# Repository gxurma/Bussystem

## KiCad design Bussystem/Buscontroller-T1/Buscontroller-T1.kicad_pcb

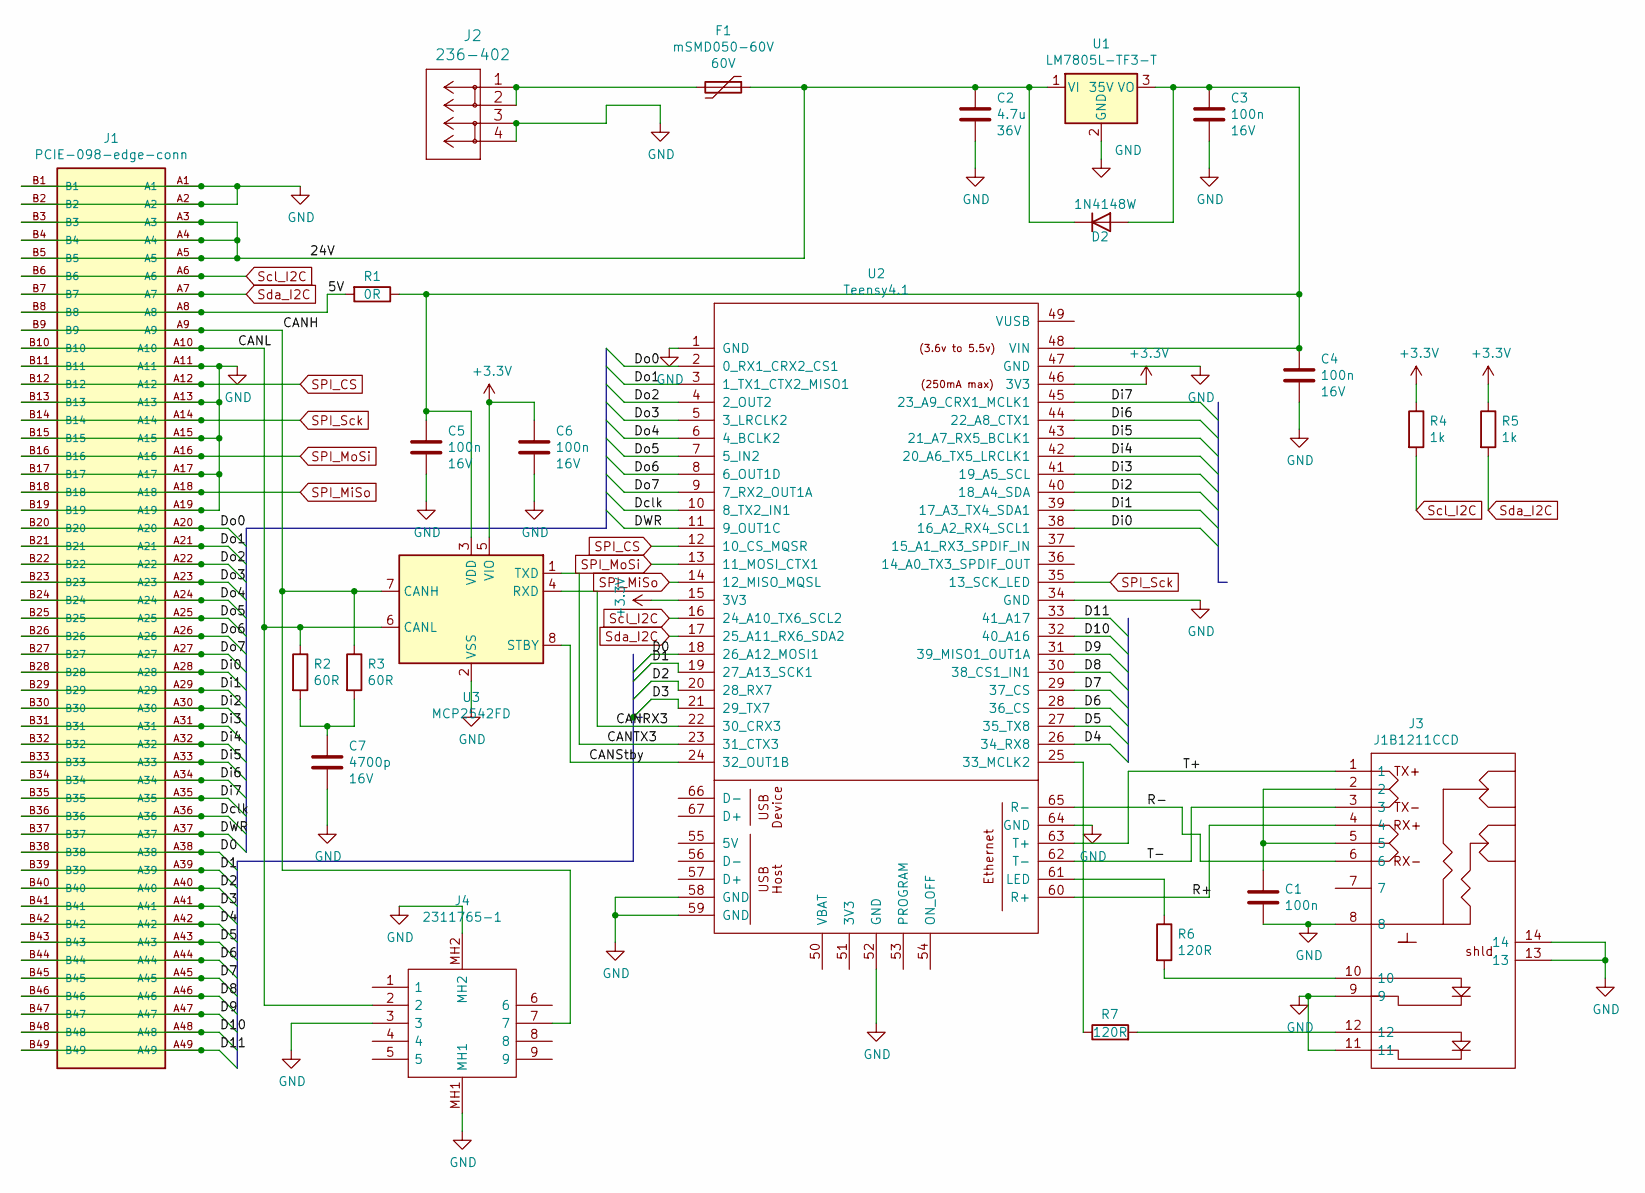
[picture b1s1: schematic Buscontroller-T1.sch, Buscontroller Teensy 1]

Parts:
C1: 100n; C_0603_HandSoldering
C2: 4.7u; C_0805_HandSoldering
C3, C4, C5, C6: 100n; C_0805_HandSoldering
C7: 4700p; C_0805_HandSoldering
D2: 1N4148W; D_SOD-123; Partnumber C81598
F1: mSMD050-60V; R_1812_HandSoldering; Partnumber C70113
J1: PCIE-098-edge-conn; pci-x_edge-x8; PARTREV D
J2: 236-402
J3: J1B1211CCD; Mouser Part Number 950-J1B1211CCD
J4: 2311765-1; 23117651; Mouser Part Number 571-2311765-1
R1: 0R; R_0805_HandSoldering
R2, R3: 60R; R_0603_HandSoldering
R4, R5: 1k; R_0603_HandSoldering
R6, R7: 120R; R_0603_HandSoldering
U1: LM7805L-TF3-T; TO-220-3_Vertical; Partnumber C71107
U2: Teensy4.1; Teensy41
U3: MCP2542FD; SOIC-8-1EP_3.9x4.9mm_Pitch1.27mm

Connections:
+3V3: C6.1, R4.1, R5.1, U2.15 (3V3), U2.46 (3V3), U3.5 (VIO)
/5V: J1.A8, J1.B8, R1.2
/24V: C2.1, D2.1 (K), F1.1, J1.A3, J1.A4, J1.A5, J1.B3, J1.B4, J1.B5, U1.1 (VI)
/CANH: J1.A9, J1.B9, J4.7, R3.1, U3.7 (CANH)
/CANL: J1.A10, J1.B10, J4.2, R2.1, U3.6 (CANL)
/CANRX3: U2.22 (30_CRX3), U3.4 (RXD)
/CANStby: U2.24 (32_OUT1B), U3.8 (STBY)
/CANTX3: U2.23 (31_CTX3), U3.1 (TXD)
/D0: J1.A38, J1.B38, U2.18 (26_A12_MOSI1)
/D1: J1.A39, J1.B39, U2.19 (27_A13_SCK1)
/D2: J1.A40, J1.B40, U2.20 (28_RX7)
/D3: J1.A41, J1.B41, U2.21 (29_TX7)
/D4: J1.A42, J1.B42, U2.26 (34_RX8)
/D5: J1.A43, J1.B43, U2.27 (35_TX8)
/D6: J1.A44, J1.B44, U2.28 (36_CS)
/D7: J1.A45, J1.B45, U2.29 (37_CS)
/D8: J1.A46, J1.B46, U2.30 (38_CS1_IN1)
/D9: J1.A47, J1.B47, U2.31 (39_MISO1_OUT1A)
/D10: J1.A48, J1.B48, U2.32 (40_A16)
/D11: J1.A49, J1.B49, U2.33 (41_A17)
/DWR: J1.A37, J1.B37, U2.11 (9_OUT1C)
/Dclk: J1.A36, J1.B36, U2.10 (8_TX2_IN1)
/Di0: J1.A28, J1.B28, U2.38 (16_A2_RX4_SCL1)
/Di1: J1.A29, J1.B29, U2.39 (17_A3_TX4_SDA1)
/Di2: J1.A30, J1.B30, U2.40 (18_A4_SDA)
/Di3: J1.A31, J1.B31, U2.41 (19_A5_SCL)
/Di4: J1.A32, J1.B32, U2.42 (20_A6_TX5_LRCLK1)
/Di5: J1.A33, J1.B33, U2.43 (21_A7_RX5_BCLK1)
/Di6: J1.A34, J1.B34, U2.44 (22_A8_CTX1)
/Di7: J1.A35, J1.B35, U2.45 (23_A9_CRX1_MCLK1)
/Do0: J1.A20, J1.B20, U2.2 (0_RX1_CRX2_CS1)
/Do1: J1.A21, J1.B21, U2.3 (1_TX1_CTX2_MISO1)
/Do2: J1.A22, J1.B22, U2.4 (2_OUT2)
/Do3: J1.A23, J1.B23, U2.5 (3_LRCLK2)
/Do4: J1.A24, J1.B24, U2.6 (4_BCLK2)
/Do5: J1.A25, J1.B25, U2.7 (5_IN2)
/Do6: J1.A26, J1.B26, U2.8 (6_OUT1D)
/Do7: J1.A27, J1.B27, U2.9 (7_RX2_OUT1A)
/R+: J3.4, U2.60 (R+)
/R-: J3.6, U2.65 (R-)
/T+: J3.1, U2.63 (T+)
/T-: J3.3, U2.62 (T-)
GND: C1.2, C2.2, C3.2, C4.2, C5.2, C6.2, C7.2, J1.A1, J1.A2, J1.A11, J1.A13, J1.A15, J1.A17, J1.A19, J1.B1, J1.B2, J1.B11, J1.B13, J1.B15, J1.B17, J1.B19, J2.3, J2.4, J3.8, J3.9, J3.11, J3.13, J3.14, J4.3, J4.MH1, J4.MH2, U1.2 (GND), U2.1 (GND), U2.34 (GND), U2.47 (GND), U2.52 (GND), U2.58 (GND), U2.59 (GND), U2.64 (GND), U3.2 (VSS), U3.9 (VSS)
unnamed: C1.1, J3.2, J3.5
unnamed: C3.1, C4.1, C5.1, D2.2 (A), R1.1, U1.3 (VO), U2.48 (VIN), U3.3 (VDD)
unnamed: C7.1, R2.2, R3.2
unnamed: F1.2, J2.1, J2.2
unnamed: J3.10, R6.2
unnamed: J3.12, R7.2
unnamed: R6.1, U2.61 (LED)
unnamed: R7.1, U2.25 (33_MCLK2)
SPI_CS: J1.A12, J1.B12, U2.12 (10_CS_MQSR)
SPI_MiSo: J1.A18, J1.B18, U2.14 (12_MISO_MQSL)
SPI_MoSi: J1.A16, J1.B16, U2.13 (11_MOSI_CTX1)
SPI_Sck: J1.A14, J1.B14, U2.35 (13_SCK_LED)
Scl_I2C: J1.A6, J1.B6, R4.2, U2.16 (24_A10_TX6_SCL2)
Sda_I2C: J1.A7, J1.B7, R5.2, U2.17 (25_A11_RX6_SDA2)

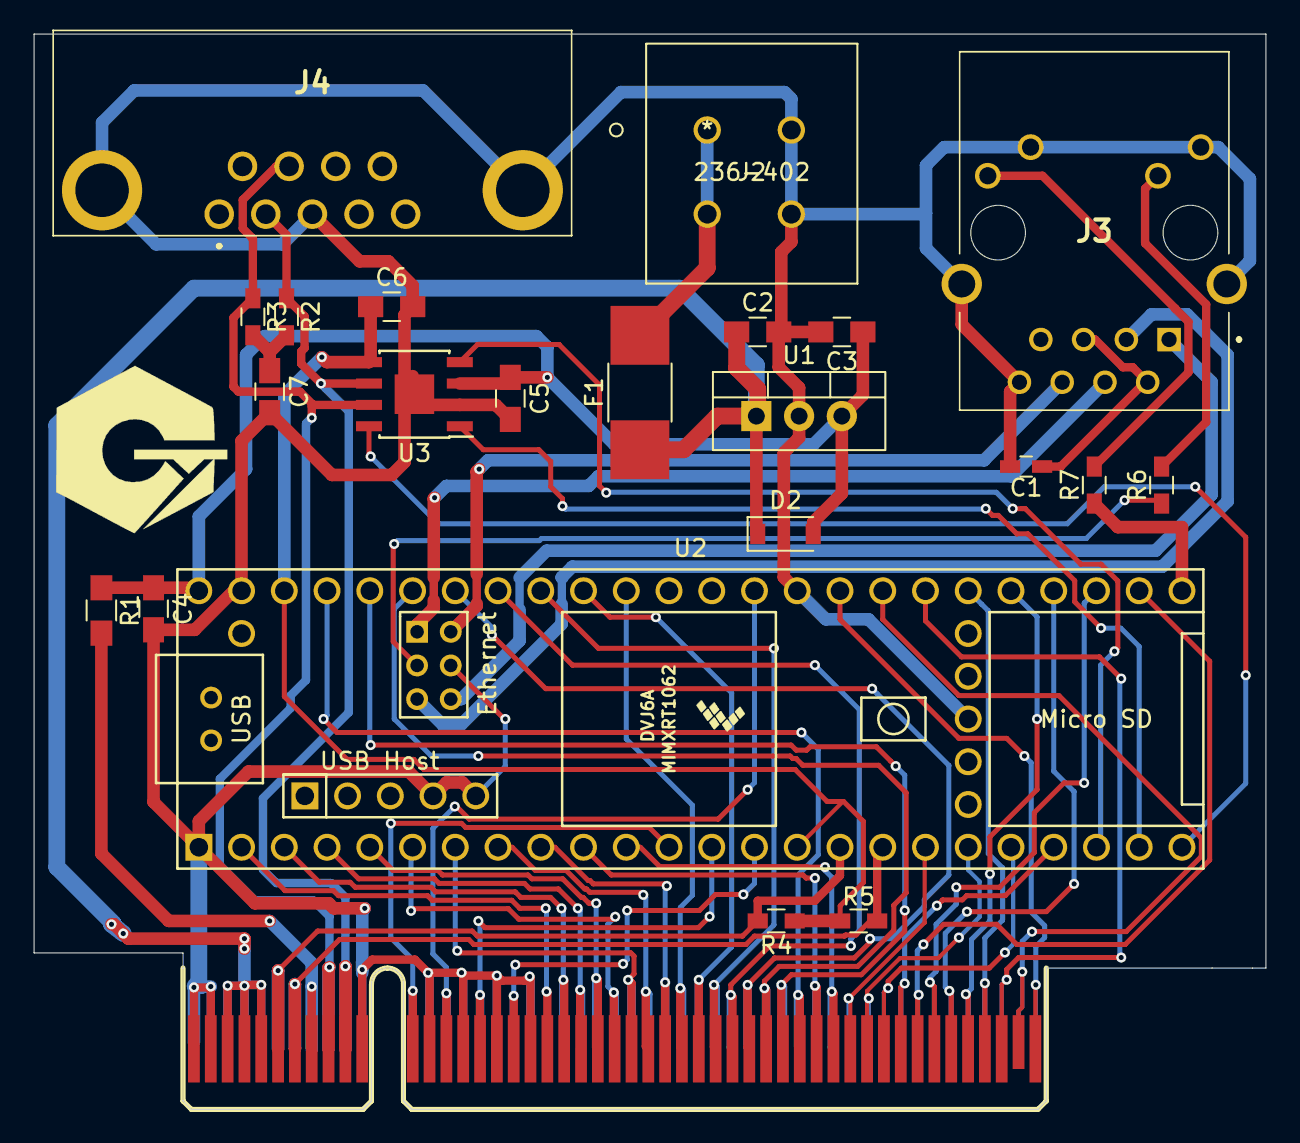
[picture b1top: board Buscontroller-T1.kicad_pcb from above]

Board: 2 copper layers, 73.2 x 63.9 mm, 23 parts (0 on the bottom side), 57 nets.

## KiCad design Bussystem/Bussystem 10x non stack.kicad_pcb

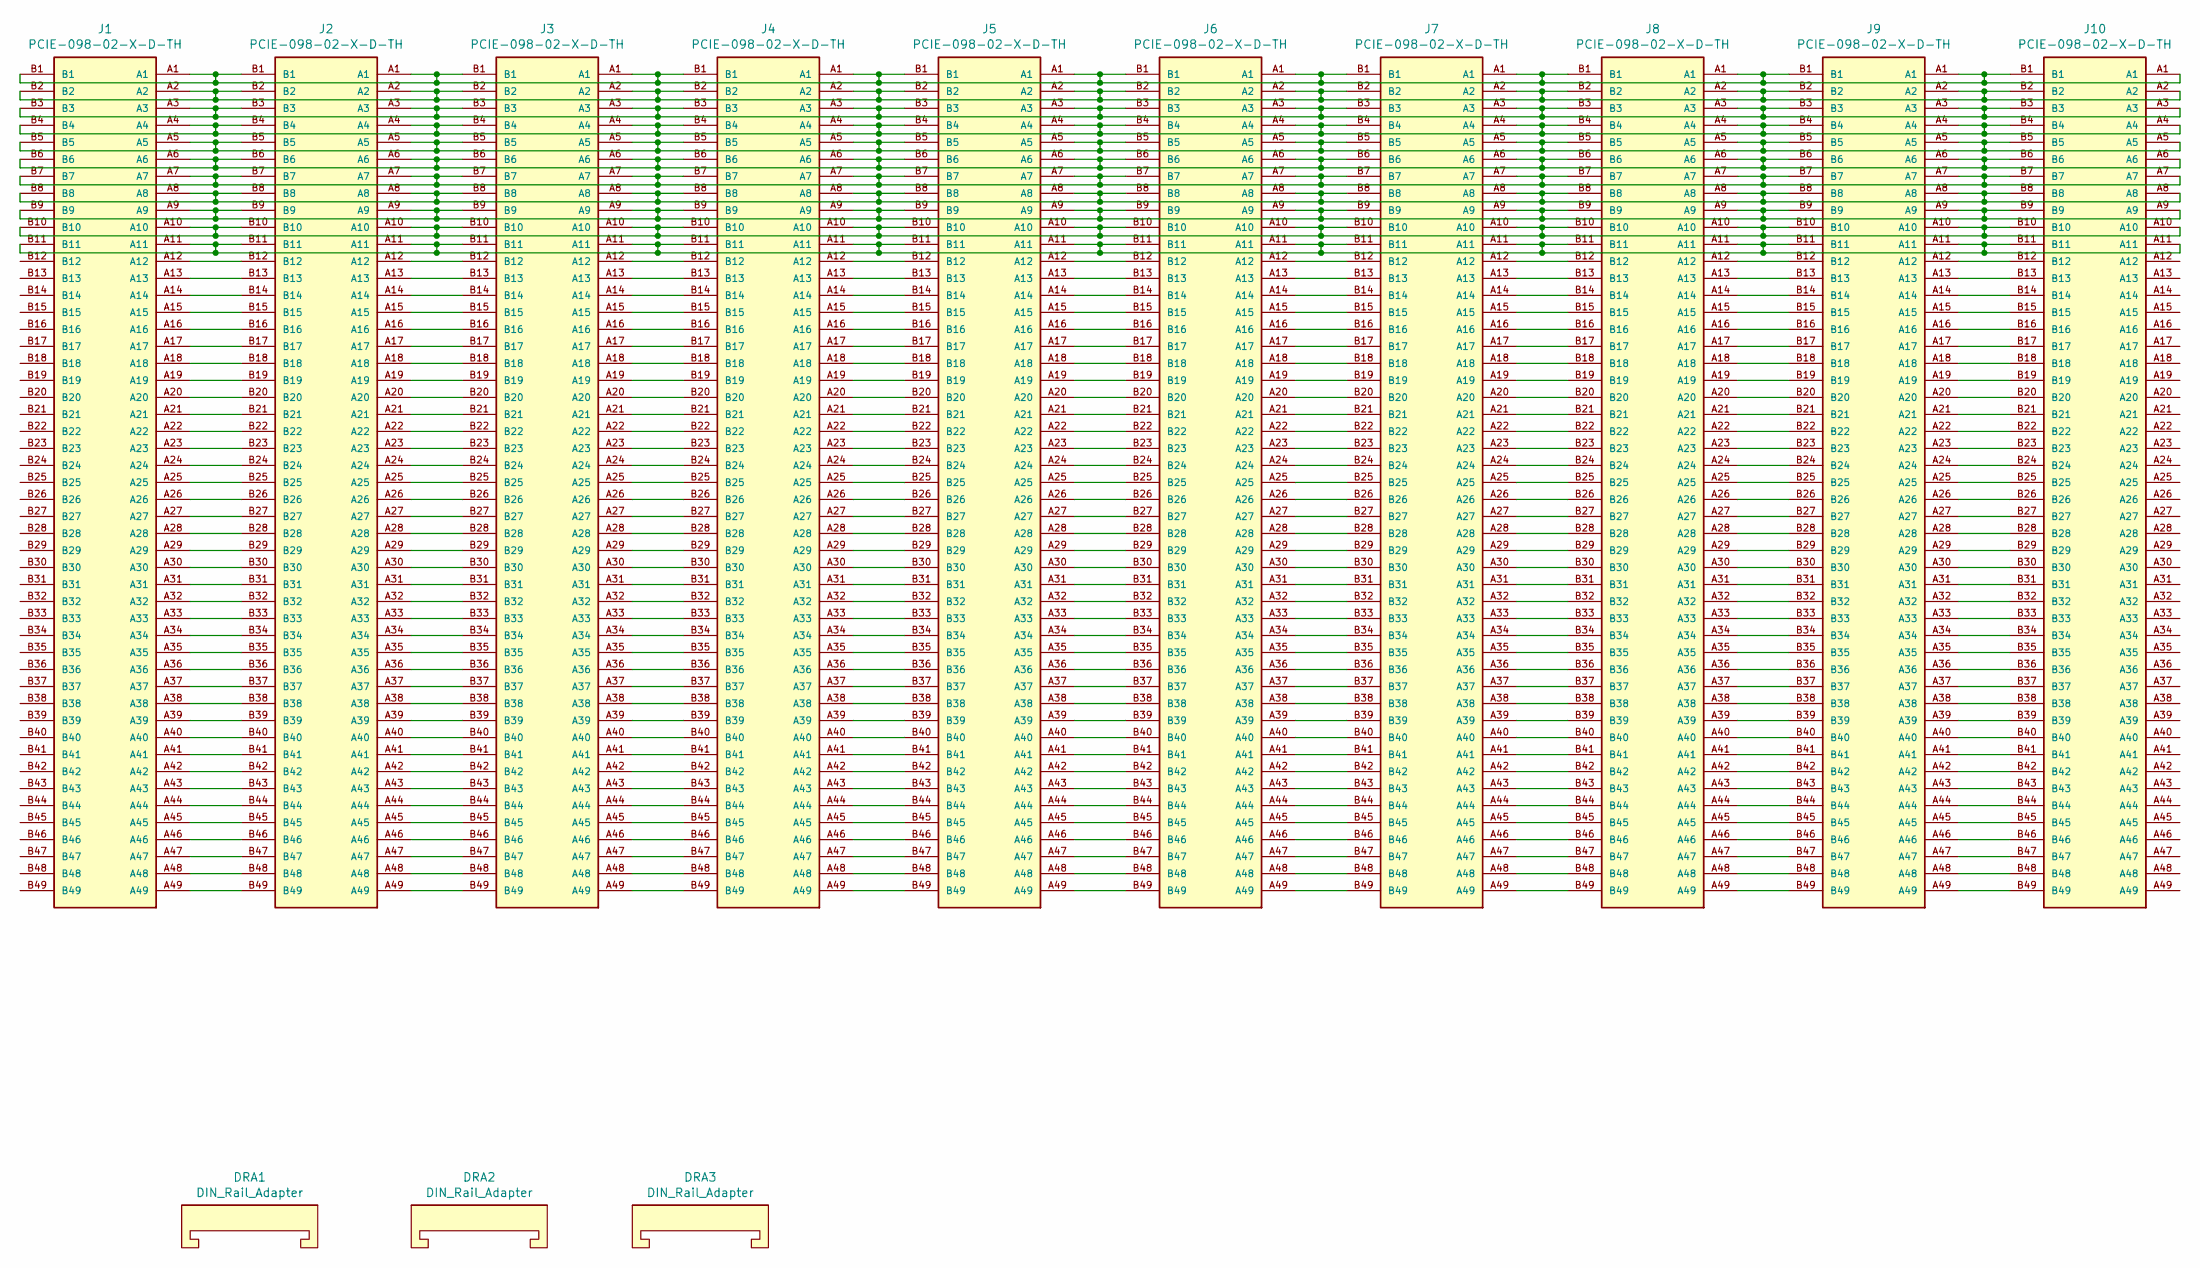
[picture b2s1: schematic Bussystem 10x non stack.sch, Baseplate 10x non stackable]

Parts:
DRA1, DRA2, DRA3: DIN_Rail_Adapter; DIN_Mount
J1, J2, J3, J4, J5, J6, J7, J8, J9, J10: PCIE-098-02-X-D-TH; SAMTEC_PCIE-098-02-X-D-TH; PARTREV D

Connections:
unnamed: J1.A1, J1.B1, J2.A1, J2.B1, J3.A1, J3.B1, J4.A1, J4.B1, J5.A1, J5.B1, J6.A1, J6.B1, J7.A1, J7.B1, J8.A1, J8.B1, J9.A1, J9.B1, J10.A1, J10.B1
unnamed: J1.A2, J1.B2, J2.A2, J2.B2, J3.A2, J3.B2, J4.A2, J4.B2, J5.A2, J5.B2, J6.A2, J6.B2, J7.A2, J7.B2, J8.A2, J8.B2, J9.A2, J9.B2, J10.A2, J10.B2
unnamed: J1.A3, J1.B3, J2.A3, J2.B3, J3.A3, J3.B3, J4.A3, J4.B3, J5.A3, J5.B3, J6.A3, J6.B3, J7.A3, J7.B3, J8.A3, J8.B3, J9.A3, J9.B3, J10.A3, J10.B3
unnamed: J1.A4, J1.B4, J2.A4, J2.B4, J3.A4, J3.B4, J4.A4, J4.B4, J5.A4, J5.B4, J6.A4, J6.B4, J7.A4, J7.B4, J8.A4, J8.B4, J9.A4, J9.B4, J10.A4, J10.B4
unnamed: J1.A5, J1.B5, J2.A5, J2.B5, J3.A5, J3.B5, J4.A5, J4.B5, J5.A5, J5.B5, J6.A5, J6.B5, J7.A5, J7.B5, J8.A5, J8.B5, J9.A5, J9.B5, J10.A5, J10.B5
unnamed: J1.A6, J1.B6, J2.A6, J2.B6, J3.A6, J3.B6, J4.A6, J4.B6, J5.A6, J5.B6, J6.A6, J6.B6, J7.A6, J7.B6, J8.A6, J8.B6, J9.A6, J9.B6, J10.A6, J10.B6
unnamed: J1.A7, J1.B7, J2.A7, J2.B7, J3.A7, J3.B7, J4.A7, J4.B7, J5.A7, J5.B7, J6.A7, J6.B7, J7.A7, J7.B7, J8.A7, J8.B7, J9.A7, J9.B7, J10.A7, J10.B7
unnamed: J1.A8, J1.B8, J2.A8, J2.B8, J3.A8, J3.B8, J4.A8, J4.B8, J5.A8, J5.B8, J6.A8, J6.B8, J7.A8, J7.B8, J8.A8, J8.B8, J9.A8, J9.B8, J10.A8, J10.B8
unnamed: J1.A9, J1.B9, J2.A9, J2.B9, J3.A9, J3.B9, J4.A9, J4.B9, J5.A9, J5.B9, J6.A9, J6.B9, J7.A9, J7.B9, J8.A9, J8.B9, J9.A9, J9.B9, J10.A9, J10.B9
unnamed: J1.A10, J1.B10, J2.A10, J2.B10, J3.A10, J3.B10, J4.A10, J4.B10, J5.A10, J5.B10, J6.A10, J6.B10, J7.A10, J7.B10, J8.A10, J8.B10, J9.A10, J9.B10, J10.A10, J10.B10
unnamed: J1.A11, J1.B11, J2.A11, J2.B11, J3.A11, J3.B11, J4.A11, J4.B11, J5.A11, J5.B11, J6.A11, J6.B11, J7.A11, J7.B11, J8.A11, J8.B11, J9.A11, J9.B11, J10.A11, J10.B11
unnamed: J1.A12, J2.B12
unnamed: J1.A13, J2.B13
unnamed: J1.A14, J2.B14
unnamed: J1.A15, J2.B15
unnamed: J1.A16, J2.B16
unnamed: J1.A17, J2.B17
unnamed: J1.A18, J2.B18
unnamed: J1.A19, J2.B19
unnamed: J1.A20, J2.B20
unnamed: J1.A21, J2.B21
unnamed: J1.A22, J2.B22
unnamed: J1.A23, J2.B23
unnamed: J1.A24, J2.B24
unnamed: J1.A25, J2.B25
unnamed: J1.A26, J2.B26
unnamed: J1.A27, J2.B27
unnamed: J1.A28, J2.B28
unnamed: J1.A29, J2.B29
unnamed: J1.A30, J2.B30
unnamed: J1.A31, J2.B31
unnamed: J1.A32, J2.B32
unnamed: J1.A33, J2.B33
unnamed: J1.A34, J2.B34
unnamed: J1.A35, J2.B35
unnamed: J1.A36, J2.B36
unnamed: J1.A37, J2.B37
unnamed: J1.A38, J2.B38
unnamed: J1.A39, J2.B39
unnamed: J1.A40, J2.B40
unnamed: J1.A41, J2.B41
unnamed: J1.A42, J2.B42
unnamed: J1.A43, J2.B43
unnamed: J1.A44, J2.B44
unnamed: J1.A45, J2.B45
unnamed: J1.A46, J2.B46
unnamed: J1.A47, J2.B47
unnamed: J1.A48, J2.B48
unnamed: J1.A49, J2.B49
unnamed: J2.A12, J3.B12
unnamed: J2.A13, J3.B13
unnamed: J2.A14, J3.B14
unnamed: J2.A15, J3.B15
unnamed: J2.A16, J3.B16
unnamed: J2.A17, J3.B17
unnamed: J2.A18, J3.B18
unnamed: J2.A19, J3.B19
unnamed: J2.A20, J3.B20
unnamed: J2.A21, J3.B21
unnamed: J2.A22, J3.B22
unnamed: J2.A23, J3.B23
unnamed: J2.A24, J3.B24
unnamed: J2.A25, J3.B25
unnamed: J2.A26, J3.B26
unnamed: J2.A27, J3.B27
unnamed: J2.A28, J3.B28
unnamed: J2.A29, J3.B29
unnamed: J2.A30, J3.B30
unnamed: J2.A31, J3.B31
unnamed: J2.A32, J3.B32
unnamed: J2.A33, J3.B33
unnamed: J2.A34, J3.B34
unnamed: J2.A35, J3.B35
unnamed: J2.A36, J3.B36
unnamed: J2.A37, J3.B37
unnamed: J2.A38, J3.B38
unnamed: J2.A39, J3.B39
unnamed: J2.A40, J3.B40
unnamed: J2.A41, J3.B41
unnamed: J2.A42, J3.B42
unnamed: J2.A43, J3.B43
unnamed: J2.A44, J3.B44
unnamed: J2.A45, J3.B45
unnamed: J2.A46, J3.B46
unnamed: J2.A47, J3.B47
unnamed: J2.A48, J3.B48
unnamed: J2.A49, J3.B49
unnamed: J3.A12, J4.B12
unnamed: J3.A13, J4.B13
unnamed: J3.A14, J4.B14
unnamed: J3.A15, J4.B15
unnamed: J3.A16, J4.B16
unnamed: J3.A17, J4.B17
unnamed: J3.A18, J4.B18
unnamed: J3.A19, J4.B19
unnamed: J3.A20, J4.B20
unnamed: J3.A21, J4.B21
unnamed: J3.A22, J4.B22
unnamed: J3.A23, J4.B23
unnamed: J3.A24, J4.B24
unnamed: J3.A25, J4.B25
unnamed: J3.A26, J4.B26
unnamed: J3.A27, J4.B27
unnamed: J3.A28, J4.B28
unnamed: J3.A29, J4.B29
unnamed: J3.A30, J4.B30
unnamed: J3.A31, J4.B31
unnamed: J3.A32, J4.B32
unnamed: J3.A33, J4.B33
unnamed: J3.A34, J4.B34
unnamed: J3.A35, J4.B35
unnamed: J3.A36, J4.B36
unnamed: J3.A37, J4.B37
unnamed: J3.A38, J4.B38
unnamed: J3.A39, J4.B39
unnamed: J3.A40, J4.B40
unnamed: J3.A41, J4.B41
unnamed: J3.A42, J4.B42
unnamed: J3.A43, J4.B43
unnamed: J3.A44, J4.B44
unnamed: J3.A45, J4.B45
unnamed: J3.A46, J4.B46
unnamed: J3.A47, J4.B47
unnamed: J3.A48, J4.B48
unnamed: J3.A49, J4.B49
unnamed: J4.A12, J5.B12
unnamed: J4.A13, J5.B13
unnamed: J4.A14, J5.B14
unnamed: J4.A15, J5.B15
unnamed: J4.A16, J5.B16
unnamed: J4.A17, J5.B17
unnamed: J4.A18, J5.B18
unnamed: J4.A19, J5.B19
unnamed: J4.A20, J5.B20
unnamed: J4.A21, J5.B21
unnamed: J4.A22, J5.B22
unnamed: J4.A23, J5.B23
unnamed: J4.A24, J5.B24
unnamed: J4.A25, J5.B25
unnamed: J4.A26, J5.B26
unnamed: J4.A27, J5.B27
unnamed: J4.A28, J5.B28
unnamed: J4.A29, J5.B29
unnamed: J4.A30, J5.B30
unnamed: J4.A31, J5.B31
unnamed: J4.A32, J5.B32
unnamed: J4.A33, J5.B33
unnamed: J4.A34, J5.B34
unnamed: J4.A35, J5.B35
unnamed: J4.A36, J5.B36
unnamed: J4.A37, J5.B37
unnamed: J4.A38, J5.B38
unnamed: J4.A39, J5.B39
unnamed: J4.A40, J5.B40
unnamed: J4.A41, J5.B41
unnamed: J4.A42, J5.B42
unnamed: J4.A43, J5.B43
unnamed: J4.A44, J5.B44
unnamed: J4.A45, J5.B45
unnamed: J4.A46, J5.B46
unnamed: J4.A47, J5.B47
unnamed: J4.A48, J5.B48
unnamed: J4.A49, J5.B49
unnamed: J5.A12, J6.B12
unnamed: J5.A13, J6.B13
unnamed: J5.A14, J6.B14
unnamed: J5.A15, J6.B15
unnamed: J5.A16, J6.B16
unnamed: J5.A17, J6.B17
unnamed: J5.A18, J6.B18
unnamed: J5.A19, J6.B19
unnamed: J5.A20, J6.B20
unnamed: J5.A21, J6.B21
unnamed: J5.A22, J6.B22
unnamed: J5.A23, J6.B23
unnamed: J5.A24, J6.B24
unnamed: J5.A25, J6.B25
unnamed: J5.A26, J6.B26
unnamed: J5.A27, J6.B27
unnamed: J5.A28, J6.B28
unnamed: J5.A29, J6.B29
unnamed: J5.A30, J6.B30
unnamed: J5.A31, J6.B31
unnamed: J5.A32, J6.B32
unnamed: J5.A33, J6.B33
unnamed: J5.A34, J6.B34
unnamed: J5.A35, J6.B35
unnamed: J5.A36, J6.B36
unnamed: J5.A37, J6.B37
unnamed: J5.A38, J6.B38
unnamed: J5.A39, J6.B39
unnamed: J5.A40, J6.B40
unnamed: J5.A41, J6.B41
unnamed: J5.A42, J6.B42
unnamed: J5.A43, J6.B43
unnamed: J5.A44, J6.B44
unnamed: J5.A45, J6.B45
unnamed: J5.A46, J6.B46
unnamed: J5.A47, J6.B47
unnamed: J5.A48, J6.B48
unnamed: J5.A49, J6.B49
unnamed: J6.A12, J7.B12
unnamed: J6.A13, J7.B13
unnamed: J6.A14, J7.B14
unnamed: J6.A15, J7.B15
unnamed: J6.A16, J7.B16
unnamed: J6.A17, J7.B17
unnamed: J6.A18, J7.B18
unnamed: J6.A19, J7.B19
unnamed: J6.A20, J7.B20
unnamed: J6.A21, J7.B21
unnamed: J6.A22, J7.B22
unnamed: J6.A23, J7.B23
unnamed: J6.A24, J7.B24
unnamed: J6.A25, J7.B25
unnamed: J6.A26, J7.B26
unnamed: J6.A27, J7.B27
unnamed: J6.A28, J7.B28
unnamed: J6.A29, J7.B29
unnamed: J6.A30, J7.B30
unnamed: J6.A31, J7.B31
unnamed: J6.A32, J7.B32
unnamed: J6.A33, J7.B33
unnamed: J6.A34, J7.B34
unnamed: J6.A35, J7.B35
unnamed: J6.A36, J7.B36
unnamed: J6.A37, J7.B37
unnamed: J6.A38, J7.B38
unnamed: J6.A39, J7.B39
unnamed: J6.A40, J7.B40
unnamed: J6.A41, J7.B41
unnamed: J6.A42, J7.B42
unnamed: J6.A43, J7.B43
unnamed: J6.A44, J7.B44
unnamed: J6.A45, J7.B45
unnamed: J6.A46, J7.B46
unnamed: J6.A47, J7.B47
unnamed: J6.A48, J7.B48
unnamed: J6.A49, J7.B49
unnamed: J7.A12, J8.B12
unnamed: J7.A13, J8.B13
unnamed: J7.A14, J8.B14
unnamed: J7.A15, J8.B15
unnamed: J7.A16, J8.B16
unnamed: J7.A17, J8.B17
unnamed: J7.A18, J8.B18
unnamed: J7.A19, J8.B19
unnamed: J7.A20, J8.B20
unnamed: J7.A21, J8.B21
unnamed: J7.A22, J8.B22
unnamed: J7.A23, J8.B23
unnamed: J7.A24, J8.B24
unnamed: J7.A25, J8.B25
unnamed: J7.A26, J8.B26
unnamed: J7.A27, J8.B27
unnamed: J7.A28, J8.B28
unnamed: J7.A29, J8.B29
unnamed: J7.A30, J8.B30
unnamed: J7.A31, J8.B31
unnamed: J7.A32, J8.B32
unnamed: J7.A33, J8.B33
unnamed: J7.A34, J8.B34
unnamed: J7.A35, J8.B35
unnamed: J7.A36, J8.B36
unnamed: J7.A37, J8.B37
unnamed: J7.A38, J8.B38
unnamed: J7.A39, J8.B39
unnamed: J7.A40, J8.B40
unnamed: J7.A41, J8.B41
unnamed: J7.A42, J8.B42
unnamed: J7.A43, J8.B43
unnamed: J7.A44, J8.B44
unnamed: J7.A45, J8.B45
unnamed: J7.A46, J8.B46
unnamed: J7.A47, J8.B47
unnamed: J7.A48, J8.B48
unnamed: J7.A49, J8.B49
unnamed: J8.A12, J9.B12
unnamed: J8.A13, J9.B13
unnamed: J8.A14, J9.B14
unnamed: J8.A15, J9.B15
unnamed: J8.A16, J9.B16
unnamed: J8.A17, J9.B17
unnamed: J8.A18, J9.B18
unnamed: J8.A19, J9.B19
unnamed: J8.A20, J9.B20
unnamed: J8.A21, J9.B21
unnamed: J8.A22, J9.B22
unnamed: J8.A23, J9.B23
unnamed: J8.A24, J9.B24
unnamed: J8.A25, J9.B25
unnamed: J8.A26, J9.B26
unnamed: J8.A27, J9.B27
unnamed: J8.A28, J9.B28
unnamed: J8.A29, J9.B29
unnamed: J8.A30, J9.B30
unnamed: J8.A31, J9.B31
unnamed: J8.A32, J9.B32
unnamed: J8.A33, J9.B33
unnamed: J8.A34, J9.B34
unnamed: J8.A35, J9.B35
unnamed: J8.A36, J9.B36
unnamed: J8.A37, J9.B37
unnamed: J8.A38, J9.B38
unnamed: J8.A39, J9.B39
unnamed: J8.A40, J9.B40
unnamed: J8.A41, J9.B41
unnamed: J8.A42, J9.B42
unnamed: J8.A43, J9.B43
unnamed: J8.A44, J9.B44
unnamed: J8.A45, J9.B45
unnamed: J8.A46, J9.B46
unnamed: J8.A47, J9.B47
unnamed: J8.A48, J9.B48
unnamed: J8.A49, J9.B49
unnamed: J9.A12, J10.B12
unnamed: J9.A13, J10.B13
unnamed: J9.A14, J10.B14
unnamed: J9.A15, J10.B15
unnamed: J9.A16, J10.B16
unnamed: J9.A17, J10.B17
unnamed: J9.A18, J10.B18
unnamed: J9.A19, J10.B19
unnamed: J9.A20, J10.B20
unnamed: J9.A21, J10.B21
unnamed: J9.A22, J10.B22
unnamed: J9.A23, J10.B23
unnamed: J9.A24, J10.B24
unnamed: J9.A25, J10.B25
unnamed: J9.A26, J10.B26
unnamed: J9.A27, J10.B27
unnamed: J9.A28, J10.B28
unnamed: J9.A29, J10.B29
unnamed: J9.A30, J10.B30
unnamed: J9.A31, J10.B31
unnamed: J9.A32, J10.B32
unnamed: J9.A33, J10.B33
unnamed: J9.A34, J10.B34
unnamed: J9.A35, J10.B35
unnamed: J9.A36, J10.B36
unnamed: J9.A37, J10.B37
unnamed: J9.A38, J10.B38
unnamed: J9.A39, J10.B39
unnamed: J9.A40, J10.B40
unnamed: J9.A41, J10.B41
unnamed: J9.A42, J10.B42
unnamed: J9.A43, J10.B43
unnamed: J9.A44, J10.B44
unnamed: J9.A45, J10.B45
unnamed: J9.A46, J10.B46
unnamed: J9.A47, J10.B47
unnamed: J9.A48, J10.B48
unnamed: J9.A49, J10.B49

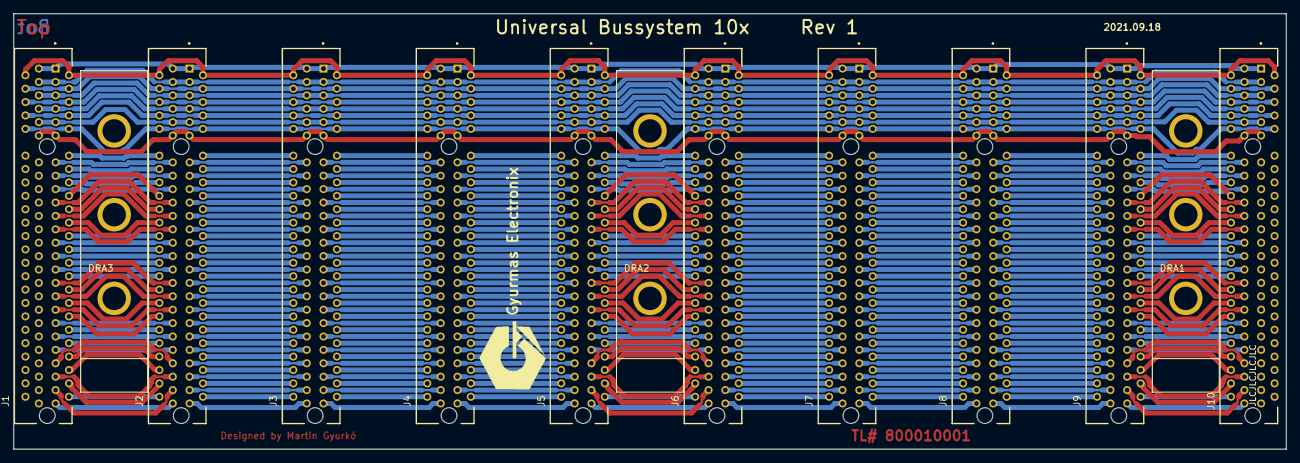
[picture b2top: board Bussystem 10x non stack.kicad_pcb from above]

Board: 2 copper layers, 190.0 x 65.0 mm, 13 parts (0 on the bottom side), 353 nets.

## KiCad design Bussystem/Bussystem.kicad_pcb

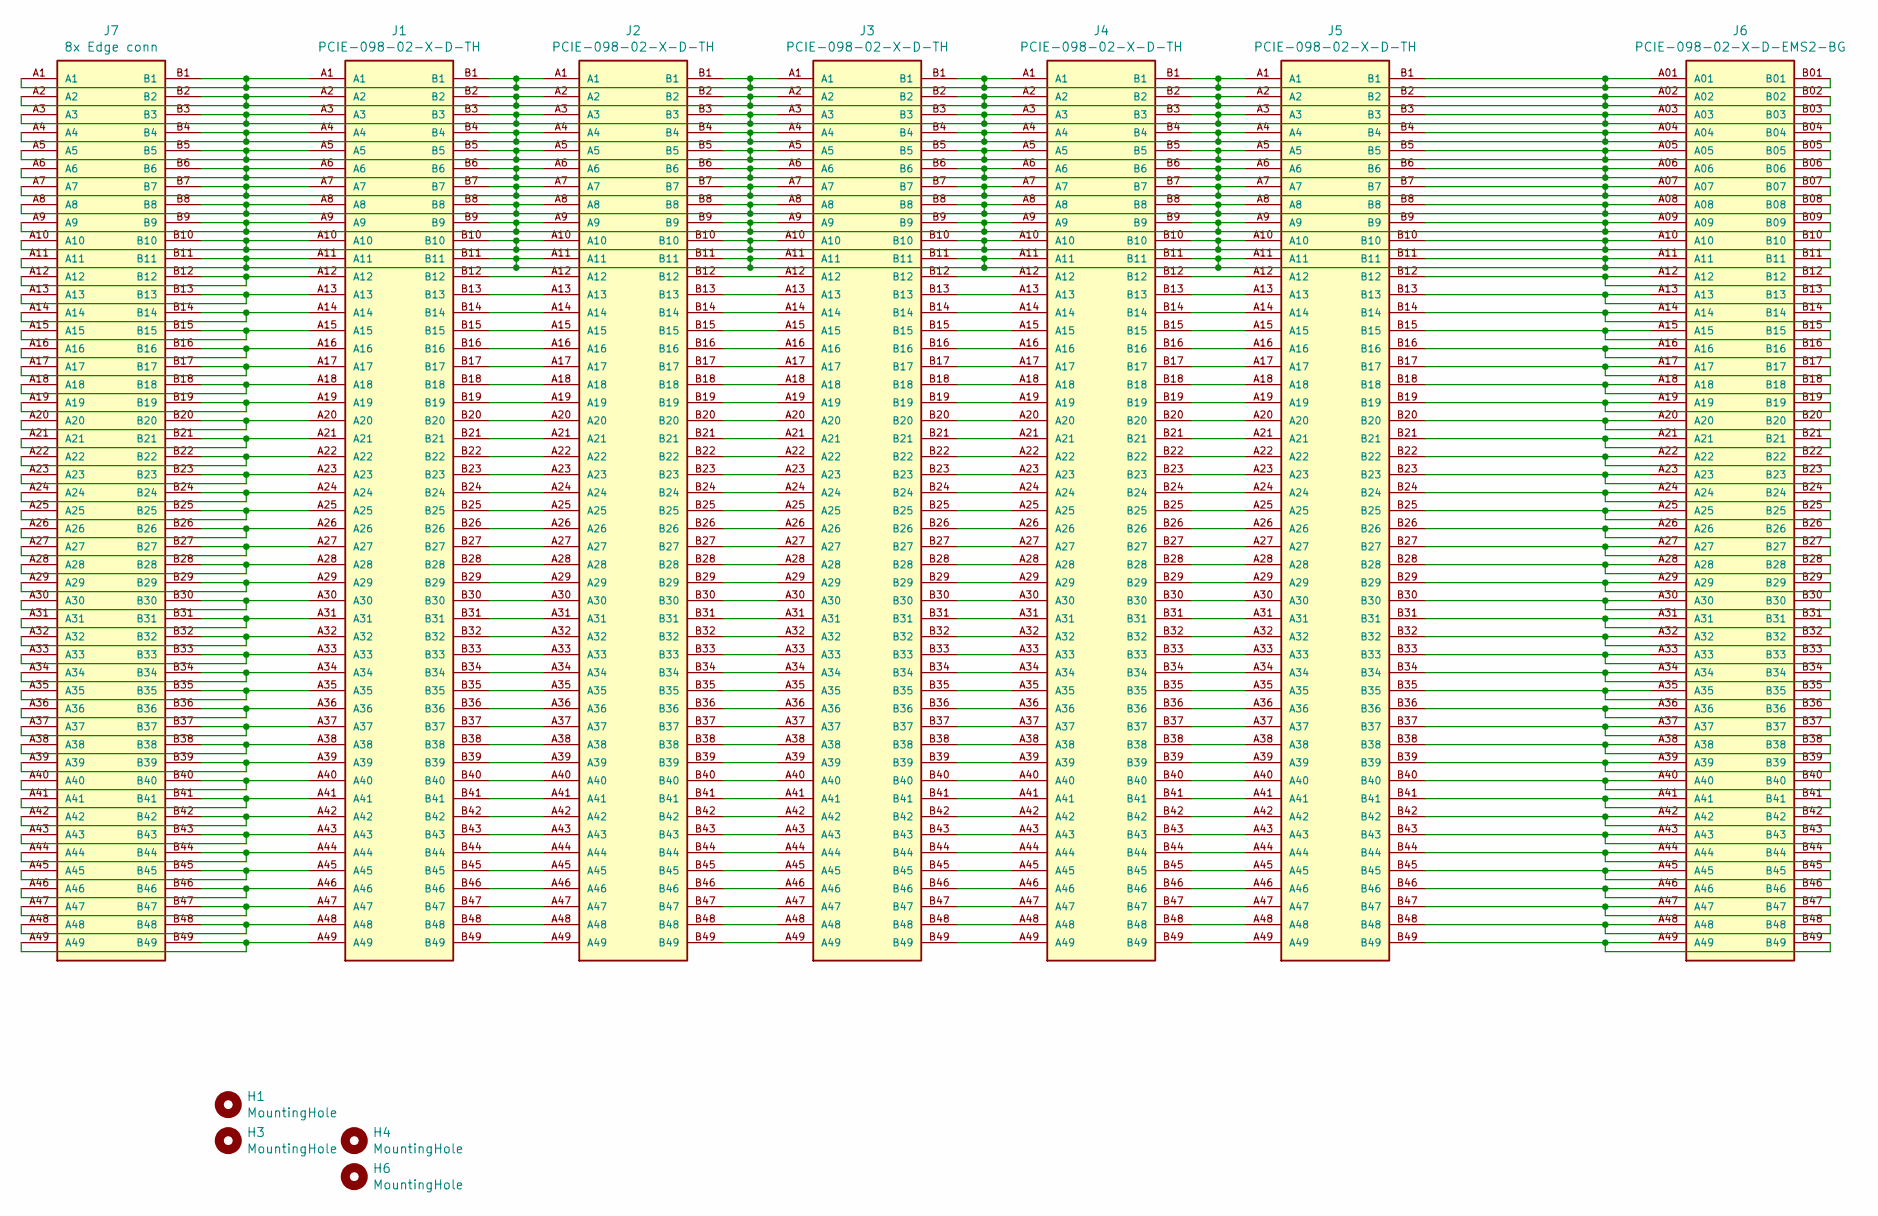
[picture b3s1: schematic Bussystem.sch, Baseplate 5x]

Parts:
H1, H3, H4, H6: MountingHole; MountingHole_3.5mm
J1, J2, J3, J4, J5: PCIE-098-02-X-D-TH; SAMTEC_PCIE-098-02-X-D-TH; PARTREV D
J6: PCIE-098-02-X-D-EMS2-BG; SAMTEC_PCIE-098-02-X-D-EMS2-BG; PARTREV C
J7: 8x Edge conn; pci-x_edge-x8; PARTREV D

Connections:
unnamed: J1.A12, J7.A12, J7.B12
unnamed: J1.A13, J7.A13, J7.B13
unnamed: J1.A14, J7.A14, J7.B14
unnamed: J1.A15, J7.A15, J7.B15
unnamed: J1.A16, J7.A16, J7.B16
unnamed: J1.A17, J7.A17, J7.B17
unnamed: J1.A18, J7.A18, J7.B18
unnamed: J1.A19, J7.A19, J7.B19
unnamed: J1.A20, J7.A20, J7.B20
unnamed: J1.A21, J7.A21, J7.B21
unnamed: J1.A22, J7.A22, J7.B22
unnamed: J1.A23, J7.A23, J7.B23
unnamed: J1.A24, J7.A24, J7.B24
unnamed: J1.A25, J7.A25, J7.B25
unnamed: J1.A26, J7.A26, J7.B26
unnamed: J1.A27, J7.A27, J7.B27
unnamed: J1.A28, J7.A28, J7.B28
unnamed: J1.A29, J7.A29, J7.B29
unnamed: J1.A30, J7.A30, J7.B30
unnamed: J1.A31, J7.A31, J7.B31
unnamed: J1.A32, J7.A32, J7.B32
unnamed: J1.A33, J7.A33, J7.B33
unnamed: J1.A34, J7.A34, J7.B34
unnamed: J1.A35, J7.A35, J7.B35
unnamed: J1.A36, J7.A36, J7.B36
unnamed: J1.A37, J7.A37, J7.B37
unnamed: J1.A38, J7.A38, J7.B38
unnamed: J1.A39, J7.A39, J7.B39
unnamed: J1.A40, J7.A40, J7.B40
unnamed: J1.A41, J7.A41, J7.B41
unnamed: J1.A42, J7.A42, J7.B42
unnamed: J1.A43, J7.A43, J7.B43
unnamed: J1.A44, J7.A44, J7.B44
unnamed: J1.A45, J7.A45, J7.B45
unnamed: J1.A46, J7.A46, J7.B46
unnamed: J1.A47, J7.A47, J7.B47
unnamed: J1.A48, J7.A48, J7.B48
unnamed: J1.A49, J7.A49, J7.B49
unnamed: J1.B12, J2.A12
unnamed: J1.B13, J2.A13
unnamed: J1.B14, J2.A14
unnamed: J1.B15, J2.A15
unnamed: J1.B16, J2.A16
unnamed: J1.B17, J2.A17
unnamed: J1.B18, J2.A18
unnamed: J1.B19, J2.A19
unnamed: J1.B20, J2.A20
unnamed: J1.B21, J2.A21
unnamed: J1.B22, J2.A22
unnamed: J1.B23, J2.A23
unnamed: J1.B24, J2.A24
unnamed: J1.B25, J2.A25
unnamed: J1.B26, J2.A26
unnamed: J1.B27, J2.A27
unnamed: J1.B28, J2.A28
unnamed: J1.B29, J2.A29
unnamed: J1.B30, J2.A30
unnamed: J1.B31, J2.A31
unnamed: J1.B32, J2.A32
unnamed: J1.B33, J2.A33
unnamed: J1.B34, J2.A34
unnamed: J1.B35, J2.A35
unnamed: J1.B36, J2.A36
unnamed: J1.B37, J2.A37
unnamed: J1.B38, J2.A38
unnamed: J1.B39, J2.A39
unnamed: J1.B40, J2.A40
unnamed: J1.B41, J2.A41
unnamed: J1.B42, J2.A42
unnamed: J1.B43, J2.A43
unnamed: J1.B44, J2.A44
unnamed: J1.B45, J2.A45
unnamed: J1.B46, J2.A46
unnamed: J1.B47, J2.A47
unnamed: J1.B48, J2.A48
unnamed: J1.B49, J2.A49
unnamed: J2.B12, J3.A12
unnamed: J2.B13, J3.A13
unnamed: J2.B14, J3.A14
unnamed: J2.B15, J3.A15
unnamed: J2.B16, J3.A16
unnamed: J2.B17, J3.A17
unnamed: J2.B18, J3.A18
unnamed: J2.B19, J3.A19
unnamed: J2.B20, J3.A20
unnamed: J2.B21, J3.A21
unnamed: J2.B22, J3.A22
unnamed: J2.B23, J3.A23
unnamed: J2.B24, J3.A24
unnamed: J2.B25, J3.A25
unnamed: J2.B26, J3.A26
unnamed: J2.B27, J3.A27
unnamed: J2.B28, J3.A28
unnamed: J2.B29, J3.A29
unnamed: J2.B30, J3.A30
unnamed: J2.B31, J3.A31
unnamed: J2.B32, J3.A32
unnamed: J2.B33, J3.A33
unnamed: J2.B34, J3.A34
unnamed: J2.B35, J3.A35
unnamed: J2.B36, J3.A36
unnamed: J2.B37, J3.A37
unnamed: J2.B38, J3.A38
unnamed: J2.B39, J3.A39
unnamed: J2.B40, J3.A40
unnamed: J2.B41, J3.A41
unnamed: J2.B42, J3.A42
unnamed: J2.B43, J3.A43
unnamed: J2.B44, J3.A44
unnamed: J2.B45, J3.A45
unnamed: J2.B46, J3.A46
unnamed: J2.B47, J3.A47
unnamed: J2.B48, J3.A48
unnamed: J2.B49, J3.A49
unnamed: J3.B12, J4.A12
unnamed: J3.B13, J4.A13
unnamed: J3.B14, J4.A14
unnamed: J3.B15, J4.A15
unnamed: J3.B16, J4.A16
unnamed: J3.B17, J4.A17
unnamed: J3.B18, J4.A18
unnamed: J3.B19, J4.A19
unnamed: J3.B20, J4.A20
unnamed: J3.B21, J4.A21
unnamed: J3.B22, J4.A22
unnamed: J3.B23, J4.A23
unnamed: J3.B24, J4.A24
unnamed: J3.B25, J4.A25
unnamed: J3.B26, J4.A26
unnamed: J3.B27, J4.A27
unnamed: J3.B28, J4.A28
unnamed: J3.B29, J4.A29
unnamed: J3.B30, J4.A30
unnamed: J3.B31, J4.A31
unnamed: J3.B32, J4.A32
unnamed: J3.B33, J4.A33
unnamed: J3.B34, J4.A34
unnamed: J3.B35, J4.A35
unnamed: J3.B36, J4.A36
unnamed: J3.B37, J4.A37
unnamed: J3.B38, J4.A38
unnamed: J3.B39, J4.A39
unnamed: J3.B40, J4.A40
unnamed: J3.B41, J4.A41
unnamed: J3.B42, J4.A42
unnamed: J3.B43, J4.A43
unnamed: J3.B44, J4.A44
unnamed: J3.B45, J4.A45
unnamed: J3.B46, J4.A46
unnamed: J3.B47, J4.A47
unnamed: J3.B48, J4.A48
unnamed: J3.B49, J4.A49
unnamed: J4.B12, J5.A12
unnamed: J4.B13, J5.A13
unnamed: J4.B14, J5.A14
unnamed: J4.B15, J5.A15
unnamed: J4.B16, J5.A16
unnamed: J4.B17, J5.A17
unnamed: J4.B18, J5.A18
unnamed: J4.B19, J5.A19
unnamed: J4.B20, J5.A20
unnamed: J4.B21, J5.A21
unnamed: J4.B22, J5.A22
unnamed: J4.B23, J5.A23
unnamed: J4.B24, J5.A24
unnamed: J4.B25, J5.A25
unnamed: J4.B26, J5.A26
unnamed: J4.B27, J5.A27
unnamed: J4.B28, J5.A28
unnamed: J4.B29, J5.A29
unnamed: J4.B30, J5.A30
unnamed: J4.B31, J5.A31
unnamed: J4.B32, J5.A32
unnamed: J4.B33, J5.A33
unnamed: J4.B34, J5.A34
unnamed: J4.B35, J5.A35
unnamed: J4.B36, J5.A36
unnamed: J4.B37, J5.A37
unnamed: J4.B38, J5.A38
unnamed: J4.B39, J5.A39
unnamed: J4.B40, J5.A40
unnamed: J4.B41, J5.A41
unnamed: J4.B42, J5.A42
unnamed: J4.B43, J5.A43
unnamed: J4.B44, J5.A44
unnamed: J4.B45, J5.A45
unnamed: J4.B46, J5.A46
unnamed: J4.B47, J5.A47
unnamed: J4.B48, J5.A48
unnamed: J4.B49, J5.A49
unnamed: J5.B12, J6.A12, J6.B12
unnamed: J5.B13, J6.A13, J6.B13
unnamed: J5.B14, J6.A14, J6.B14
unnamed: J5.B15, J6.A15, J6.B15
unnamed: J5.B16, J6.A16, J6.B16
unnamed: J5.B17, J6.A17, J6.B17
unnamed: J5.B18, J6.A18, J6.B18
unnamed: J5.B19, J6.A19, J6.B19
unnamed: J5.B20, J6.A20, J6.B20
unnamed: J5.B21, J6.A21, J6.B21
unnamed: J5.B22, J6.A22, J6.B22
unnamed: J5.B23, J6.A23, J6.B23
unnamed: J5.B24, J6.A24, J6.B24
unnamed: J5.B25, J6.A25, J6.B25
unnamed: J5.B26, J6.A26, J6.B26
unnamed: J5.B27, J6.A27, J6.B27
unnamed: J5.B28, J6.A28, J6.B28
unnamed: J5.B29, J6.A29, J6.B29
unnamed: J5.B30, J6.A30, J6.B30
unnamed: J5.B31, J6.A31, J6.B31
unnamed: J5.B32, J6.A32, J6.B32
unnamed: J5.B33, J6.A33, J6.B33
unnamed: J5.B34, J6.A34, J6.B34
unnamed: J5.B35, J6.A35, J6.B35
unnamed: J5.B36, J6.A36, J6.B36
unnamed: J5.B37, J6.A37, J6.B37
unnamed: J5.B38, J6.A38, J6.B38
unnamed: J5.B39, J6.A39, J6.B39
unnamed: J5.B40, J6.A40, J6.B40
unnamed: J5.B41, J6.A41, J6.B41
unnamed: J5.B42, J6.A42, J6.B42
unnamed: J5.B43, J6.A43, J6.B43
unnamed: J5.B44, J6.A44, J6.B44
unnamed: J5.B45, J6.A45, J6.B45
unnamed: J5.B46, J6.A46, J6.B46
unnamed: J5.B47, J6.A47, J6.B47
unnamed: J5.B48, J6.A48, J6.B48
unnamed: J5.B49, J6.A49, J6.B49

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
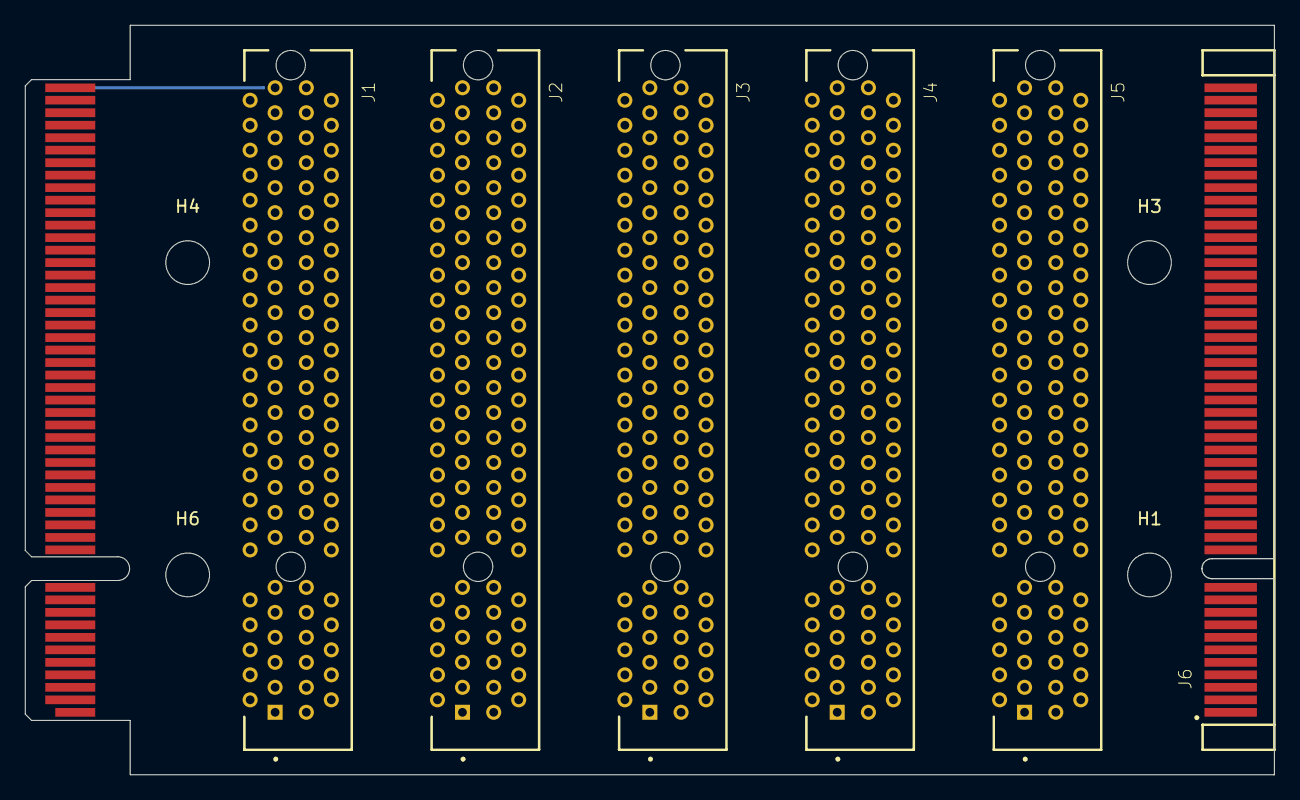
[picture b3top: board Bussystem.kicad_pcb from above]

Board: 2 copper layers, 100.0 x 60.0 mm, 11 parts (1 on the bottom side), 294 nets.

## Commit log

2021-06-20 first Baseplate design started, added bom too
2021-06-21 lanes
2021-06-30 some step files and additional editing of the sch
2021-07-05 first 10x Bus baseplate design. Still needs some redesign
2021-07-08 Had to change pitch to 20mm because wago236-416 wouldnt fit.
2021-07-12 new Teensy4 buscontroller added
2021-07-12 added some useful PDFs
2021-07-15 Some PDFs for the iMX.RT1010
2021-10-05 some new parts in the Buscontroller T1
2021-10-10 erstes import zum Layouten von Buscontroller
2021-11-03 buscontroller T1 fertig
2021-12-21 added some datasheet
2022-01-20 added digital in card

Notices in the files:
parts and their libraries:
Copyright 2021 Accelerated Designs. All rights reserved.
